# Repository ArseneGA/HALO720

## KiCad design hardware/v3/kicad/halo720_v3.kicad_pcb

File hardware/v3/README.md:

# HALO 720 v3 — cartes électroniques (rév. A)

- `kicad/` : carte principale CM4, 4 couches, 43 × 69,5 mm (KiCad 9). `kicad_flash/` : carte flash aluminium 24 × 14 mm.
- `fabrication/carte_CM4/` et `fabrication/flash/` : **fichiers à envoyer à l'usine** (Gerber zip, BOM, CPL, PDF, rendus 3D).
- `tools/` : tout est généré par script, du schéma aux fichiers d'usine.

Chaîne complète (KiCad 9 + Python 3, scipy, matplotlib) :

```bash
cd hardware/v3/tools
python3 gen_schematic.py ../kicad        # schémas des 2 cartes
python3 check_netlist.py; python3 check_netlist.py flash   # câblage = description
python3 gen_footprints.py                # empreintes DF40 (CM4), LED OSRAM
bash run_main.sh && python3 silk_main.py # placement + routage carte CM4 (≈ 10 min), DRC
python3 build_flash.py                   # carte flash, DRC
python3 make_fab.py                      # ERC + DRC + PDF schémas + Gerber/BOM/CPL/rendus (refuse si erreur)
```

Documentation : `docs/v3/SCHEMA_V3.md` (français), `docs/v3/FACTORY_ASSEMBLY_EN.md` (usine, anglais),
`docs/v3/IMAGE_EMMC.md`, `docs/v3/QUOTE_REQUEST_EN.md`. Logiciel : `camera/` et `camera/v3/`.
Brochage CM4 et empreintes DF40 repris de la carte officielle CM4IO (Raspberry Pi, CC BY 4.0).

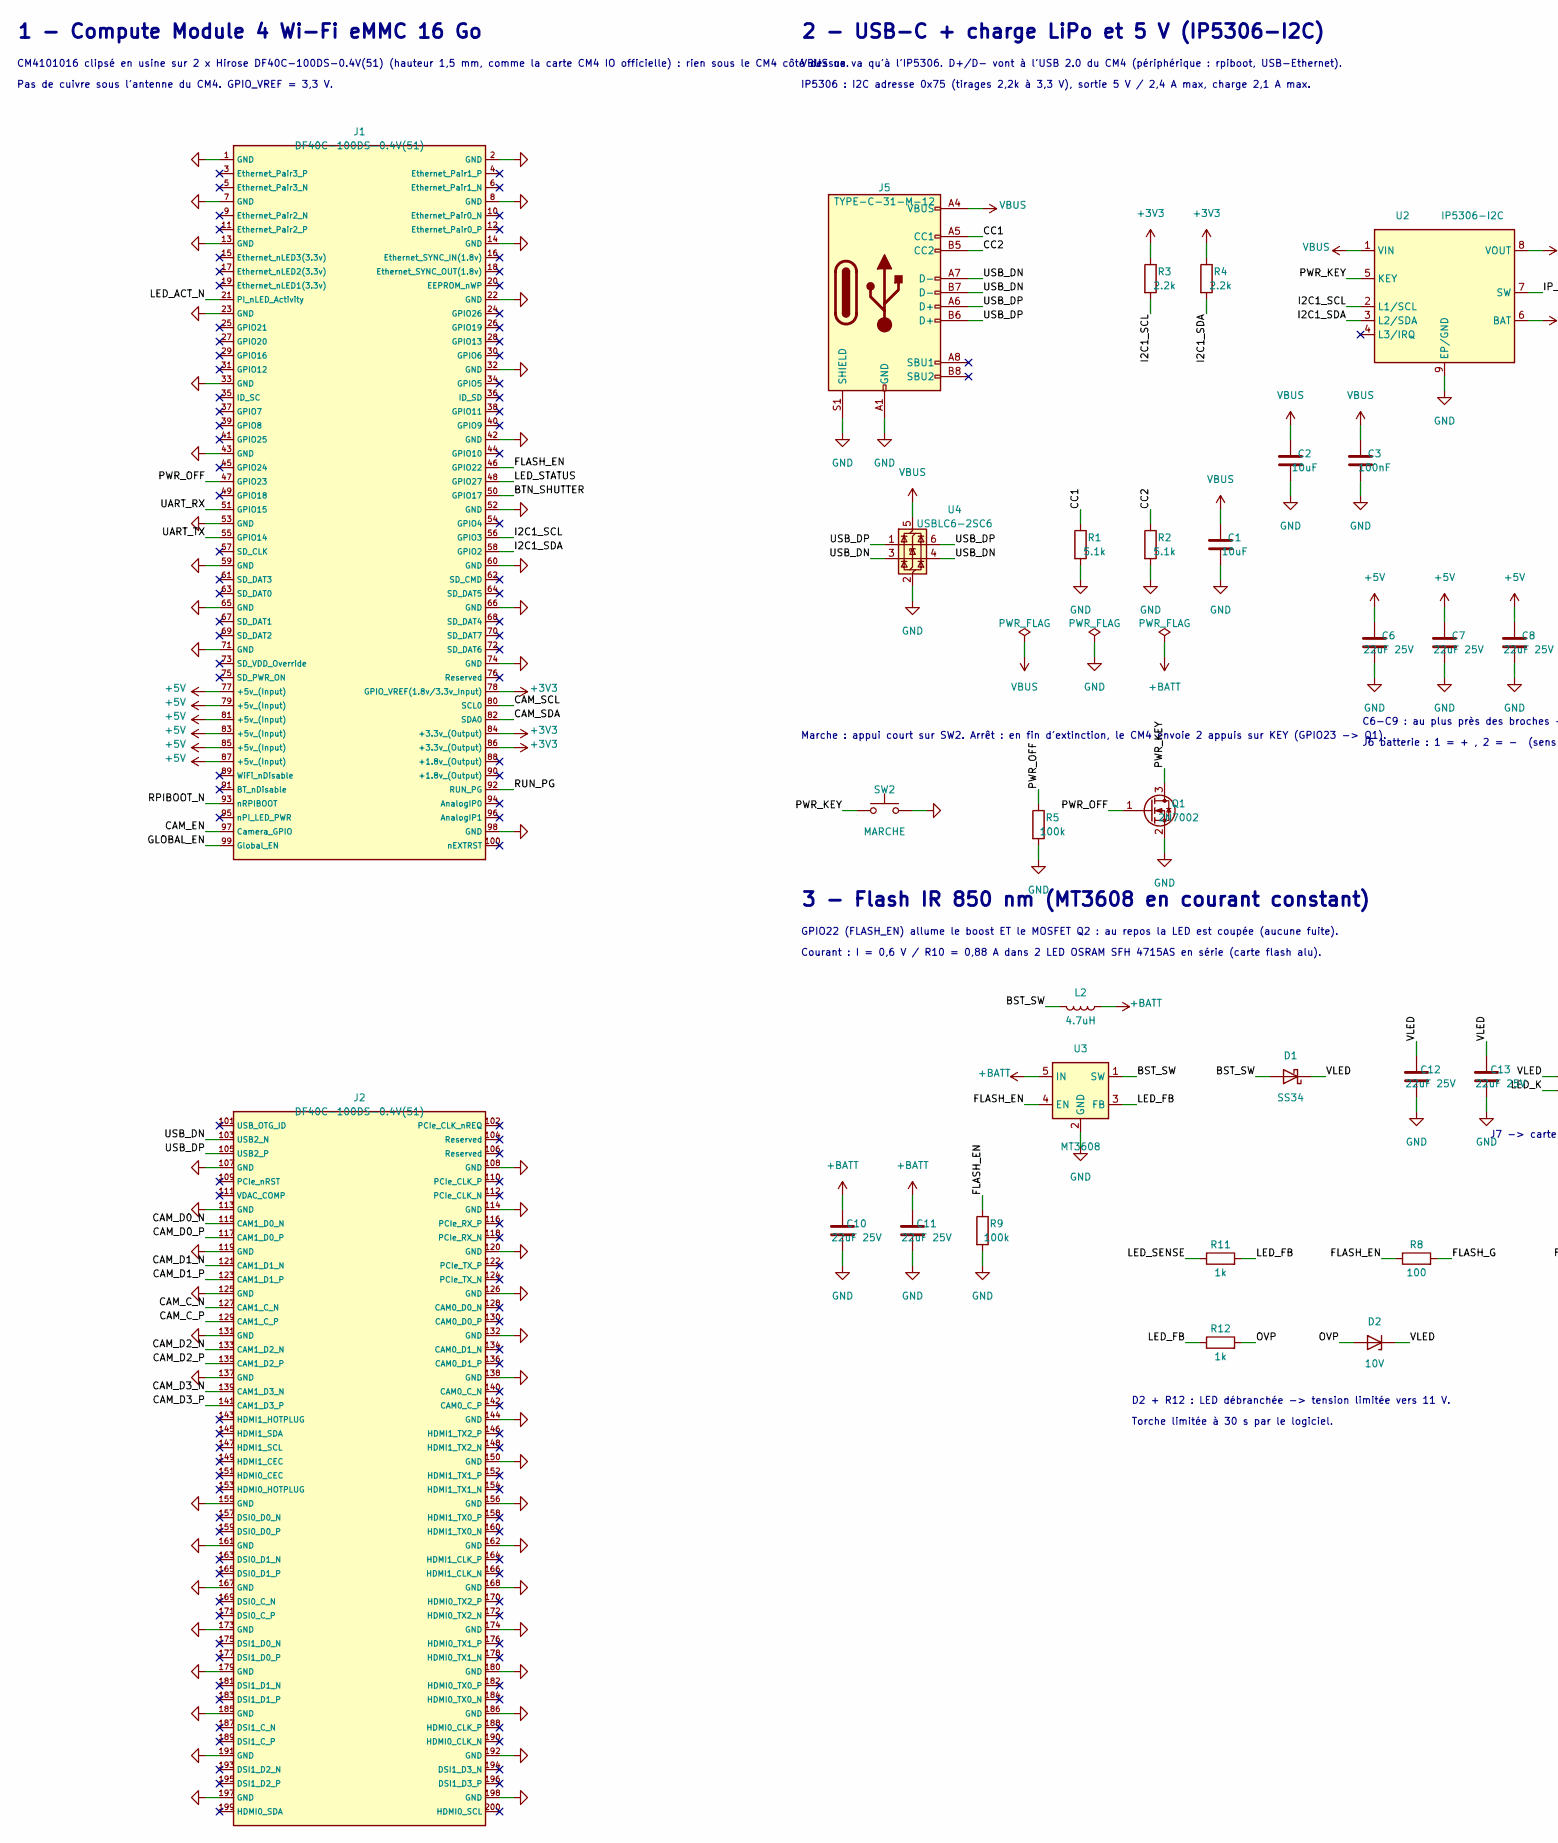
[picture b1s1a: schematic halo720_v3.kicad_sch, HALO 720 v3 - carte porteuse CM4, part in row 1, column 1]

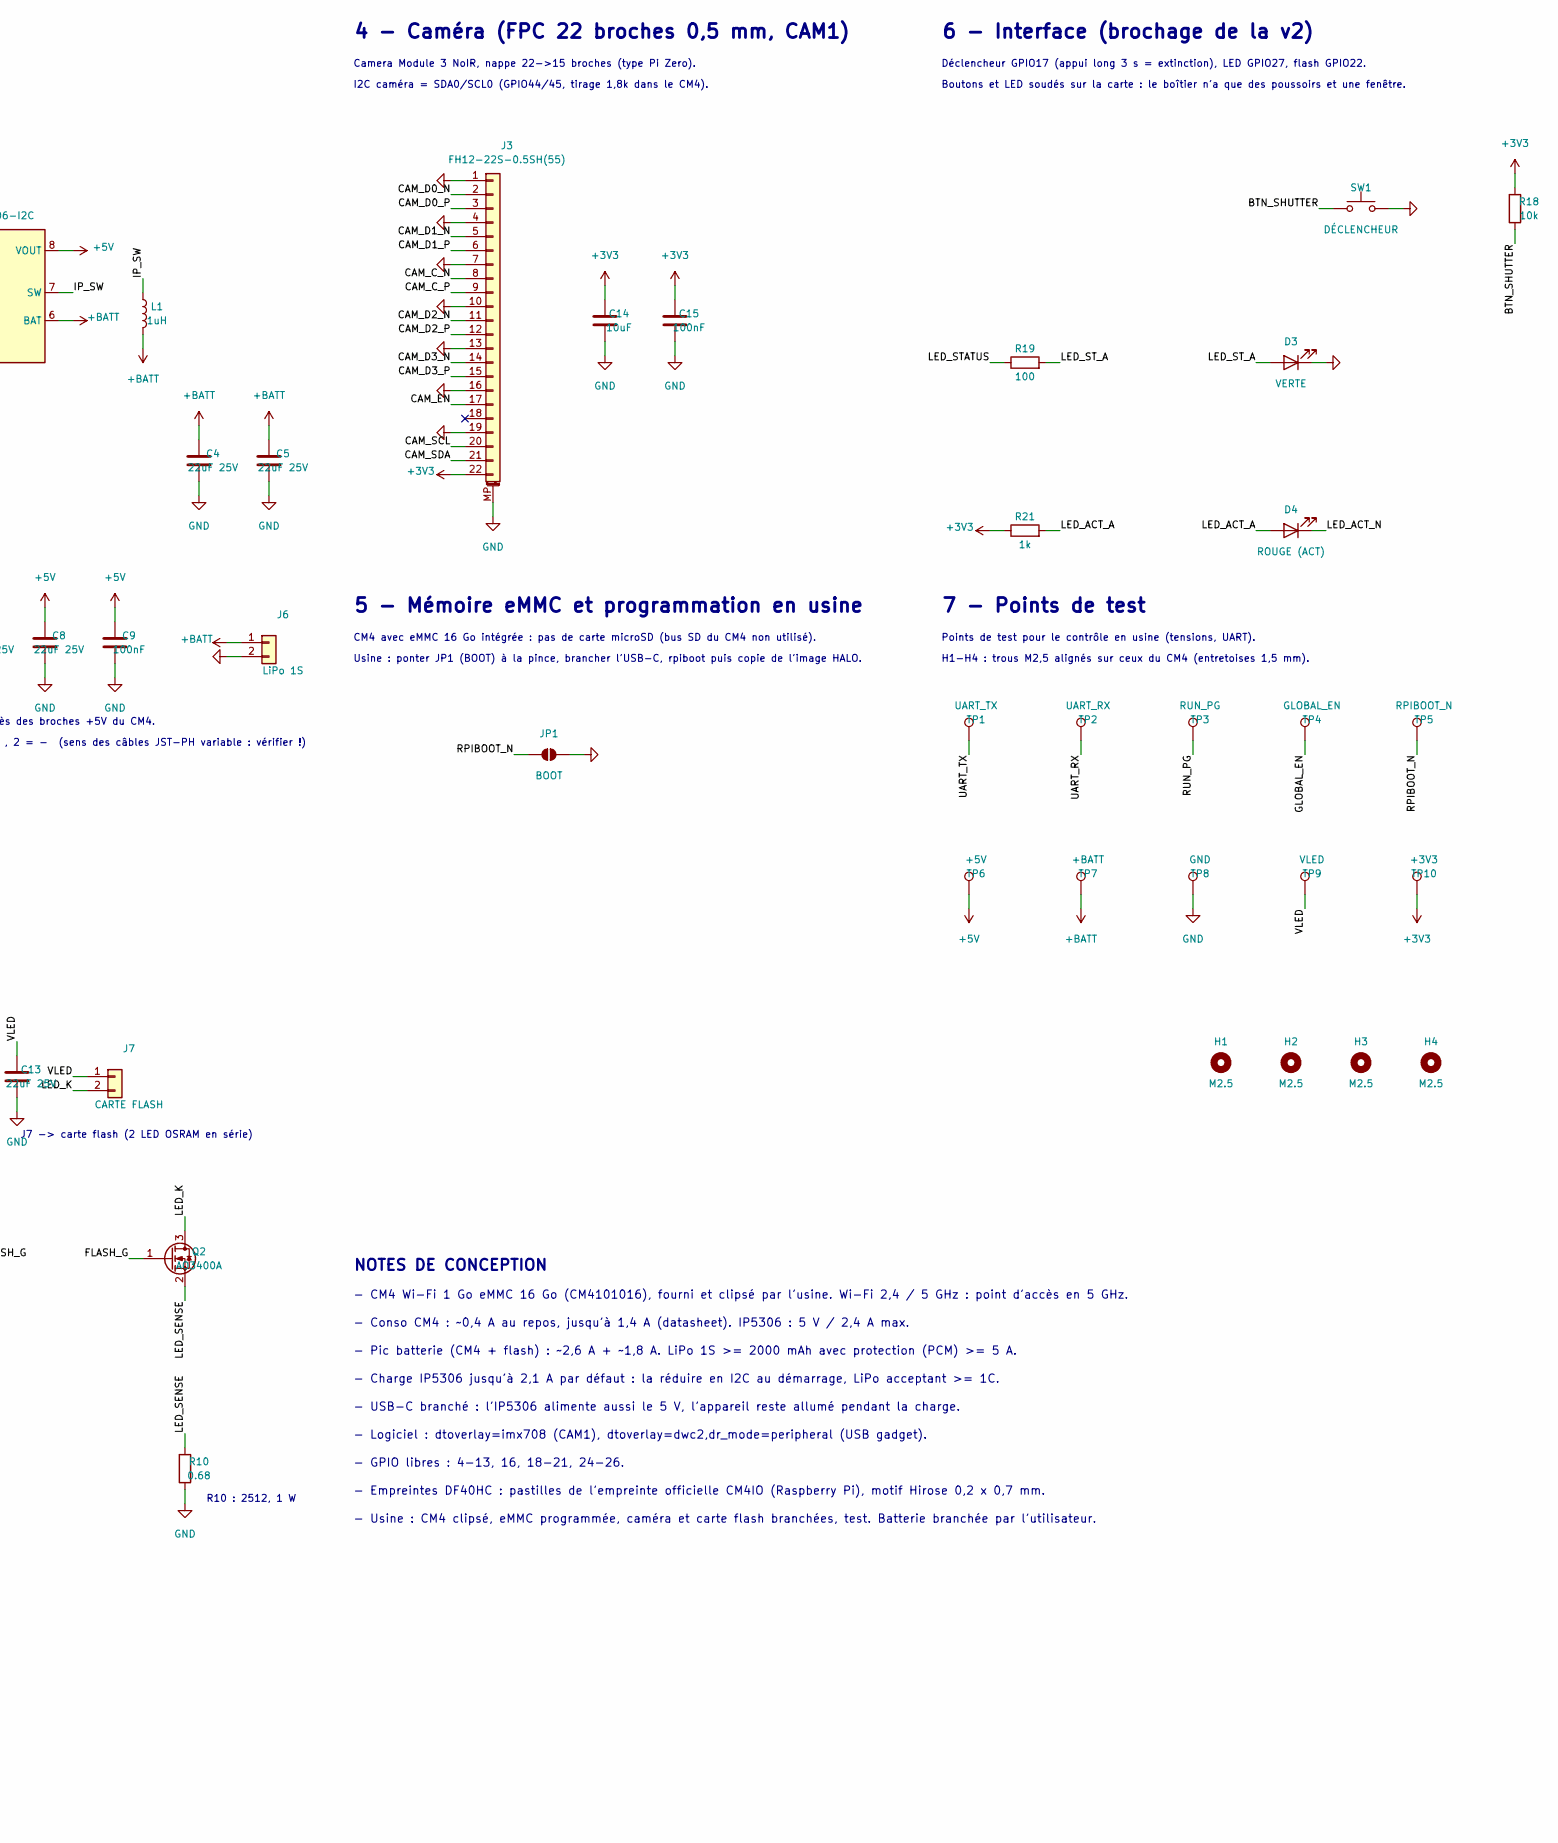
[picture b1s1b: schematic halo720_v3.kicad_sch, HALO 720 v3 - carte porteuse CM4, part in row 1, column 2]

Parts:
C1, C2, C14: 10uF; C_0603_1608Metric; LCSC C19702
C3, C9, C15: 100nF; C_0402_1005Metric; LCSC C1525
C4, C5, C6, C7, C8, C10, C11, C12, C13: 22uF 25V; C_0805_2012Metric; LCSC C45783
D1: SS34; D_SMA; MPN SS34; LCSC C8678
D2: 10V; D_SOD-123; MPN BZT52C10; LCSC C2103
D3: VERTE; LED_0603_1608Metric; MPN KT-0603G; LCSC C12624
D4: ROUGE (ACT); LED_0603_1608Metric; MPN KT-0603R; LCSC C2286
H1, H2, H3, H4: M2.5; MountingHole_2.7mm_M2.5
J1: DF40C-100DS-0.4V(51); Hirose_DF40HC3.0-100DS_CM4_J1; MPN DF40C-100DS-0.4V(51); LCSC C597931
J2: DF40C-100DS-0.4V(51); Hirose_DF40HC3.0-100DS_CM4_J2; MPN DF40C-100DS-0.4V(51); LCSC C597931
J3: FH12-22S-0.5SH(55); Hirose_FH12-22S-0.5SH_1x22-1MP_P0.50mm_Horizontal; MPN FH12-22S-0.5SH(55); LCSC C597981
J5: TYPE-C-31-M-12; USB_C_Receptacle_HRO_TYPE-C-31-M-12; MPN TYPE-C-31-M-12; LCSC C165948
J6: LiPo 1S; JST_PH_S2B-PH-SM4-TB_1x02-1MP_P2.00mm_Horizontal; MPN S2B-PH-SM4-TB(LF)(SN); LCSC C295747
J7: CARTE FLASH; JST_PH_S2B-PH-SM4-TB_1x02-1MP_P2.00mm_Horizontal; MPN S2B-PH-SM4-TB(LF)(SN); LCSC C295747
JP1: BOOT; SolderJumper-2_P1.3mm_Open_RoundedPad1.0x1.5mm
L1: 1uH; L_Changjiang_FNR6045S; MPN SMNR6045-1R0M; LCSC C135299
L2: 4.7uH; L_Sunlord_MWSA0518S; MPN SRP5030T-4R7M; LCSC C2045677
Q1: 2N7002; SOT-23; MPN 2N7002; LCSC C8545
Q2: AO3400A; SOT-23; MPN AO3400A; LCSC C20917
R1, R2: 5.1k; R_0402_1005Metric; LCSC C25905
R3, R4: 2.2k; R_0402_1005Metric; LCSC C25879
R5, R9: 100k; R_0402_1005Metric; LCSC C25741
R8, R19: 100; R_0402_1005Metric; LCSC C25076
R10: 0.68; R_2512_6332Metric; MPN RL2512FK-070R68L; LCSC C705617
R11, R12, R21: 1k; R_0402_1005Metric; LCSC C11702
R18: 10k; R_0402_1005Metric; LCSC C25744
SW1: DÉCLENCHEUR; SW_Push_1P1T_XKB_TS-1187A; MPN TS-1187A-B-A-B; LCSC C318884
SW2: MARCHE; SW_Push_1P1T_XKB_TS-1187A; MPN TS-1187A-B-A-B; LCSC C318884
TP1: UART_TX; TestPoint_Pad_D1.0mm
TP2: UART_RX; TestPoint_Pad_D1.0mm
TP3: RUN_PG; TestPoint_Pad_D1.0mm
TP4: GLOBAL_EN; TestPoint_Pad_D1.0mm
TP5: RPIBOOT_N; TestPoint_Pad_D1.0mm
TP6: +5V; TestPoint_Pad_D1.0mm
TP7: +BATT; TestPoint_Pad_D1.0mm
TP8: GND; TestPoint_Pad_D1.0mm
TP9: VLED; TestPoint_Pad_D1.0mm
TP10: +3V3; TestPoint_Pad_D1.0mm
U2: IP5306-I2C; SOIC-8-1EP_3.9x4.9mm_P1.27mm_EP2.41x3.3mm_ThermalVias; MPN IP5306-I2C; LCSC C488349
U3: MT3608; SOT-23-6; MPN MT3608; LCSC C84817
U4: USBLC6-2SC6; SOT-23-6; MPN USBLC6-2SC6; LCSC C7519

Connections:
+3V3: C14.1, C15.1, J1.78 (GPIO_VREF(1.8v/3.3v_Input)), J1.84 (+3.3v_(Output)), J1.86 (+3.3v_(Output)), J3.22, R3.1, R4.1, R18.1, R21.1, TP10.1
+5V: C6.1, C7.1, C8.1, C9.1, J1.77 (+5v_(Input)), J1.79 (+5v_(Input)), J1.81 (+5v_(Input)), J1.83 (+5v_(Input)), J1.85 (+5v_(Input)), J1.87 (+5v_(Input)), TP6.1, U2.8 (VOUT)
+BATT: C4.1, C5.1, C10.1, C11.1, J6.1, L1.2, L2.1, TP7.1, U2.6 (BAT), U3.5 (IN)
/BST_SW: D1.2 (A), L2.2, U3.1 (SW)
/BTN_SHUTTER: J1.50 (GPIO17), R18.2, SW1.1
/CAM_C_N: J2.127 (CAM1_C_N), J3.8
/CAM_C_P: J2.129 (CAM1_C_P), J3.9
/CAM_D0_N: J2.115 (CAM1_D0_N), J3.2
/CAM_D0_P: J2.117 (CAM1_D0_P), J3.3
/CAM_D1_N: J2.121 (CAM1_D1_N), J3.5
/CAM_D1_P: J2.123 (CAM1_D1_P), J3.6
/CAM_D2_N: J2.133 (CAM1_D2_N), J3.11
/CAM_D2_P: J2.135 (CAM1_D2_P), J3.12
/CAM_D3_N: J2.139 (CAM1_D3_N), J3.14
/CAM_D3_P: J2.141 (CAM1_D3_P), J3.15
/CAM_EN: J1.97 (Camera_GPIO), J3.17
/CAM_SCL: J1.80 (SCL0), J3.20
/CAM_SDA: J1.82 (SDA0), J3.21
/CC1: J5.A5 (CC1), R1.1
/CC2: J5.B5 (CC2), R2.1
/FLASH_EN: J1.46 (GPIO22), R8.1, R9.1, U3.4 (EN)
/FLASH_G: Q2.1 (G), R8.2
/GLOBAL_EN: J1.99 (Global_EN), TP4.1
/I2C1_SCL: J1.56 (GPIO3), R3.2, U2.2 (L1/SCL)
/I2C1_SDA: J1.58 (GPIO2), R4.2, U2.3 (L2/SDA)
/IP_SW: L1.1, U2.7 (SW)
/LED_ACT_A: D4.2 (A), R21.2
/LED_ACT_N: D4.1 (K), J1.21 (PI_nLED_Activity)
/LED_FB: R11.2, R12.1, U3.3 (FB)
/LED_K: J7.2, Q2.3 (D)
/LED_SENSE: Q2.2 (S), R10.1, R11.1
/LED_STATUS: J1.48 (GPIO27), R19.1
/LED_ST_A: D3.2 (A), R19.2
/OVP: D2.2 (A), R12.2
/PWR_KEY: Q1.3 (D), SW2.1, U2.5 (KEY)
/PWR_OFF: J1.47 (GPIO23), Q1.1 (G), R5.1
/RPIBOOT_N: J1.93 (nRPIBOOT), JP1.1 (A), TP5.1
/RUN_PG: J1.92 (RUN_PG), TP3.1
/UART_RX: J1.51 (GPIO15), TP2.1
/UART_TX: J1.55 (GPIO14), TP1.1
/USB_DN: J2.103 (USB2_N), J5.A7 (D-), J5.B7 (D-), U4.3 (I/O2), U4.4 (I/O2)
/USB_DP: J2.105 (USB2_P), J5.A6 (D+), J5.B6 (D+), U4.1 (I/O1), U4.6 (I/O1)
/VLED: C12.1, C13.1, D1.1 (K), D2.1 (K), J7.1, TP9.1
GND: C1.2, C2.2, C3.2, C4.2, C5.2, C6.2, C7.2, C8.2, C9.2, C10.2, C11.2, C12.2, C13.2, C14.2, C15.2, D3.1 (K), J1.1 (GND), J1.2 (GND), J1.7 (GND), J1.8 (GND), J1.13 (GND), J1.14 (GND), J1.22 (GND), J1.23 (GND), J1.32 (GND), J1.33 (GND), J1.42 (GND), J1.43 (GND), J1.52 (GND), J1.53 (GND), J1.59 (GND), J1.60 (GND), J1.65 (GND), J1.66 (GND), J1.71 (GND), J1.74 (GND), J1.98 (GND), J2.107 (GND), J2.108 (GND), J2.113 (GND), J2.114 (GND), J2.119 (GND), J2.120 (GND), J2.125 (GND), J2.126 (GND), J2.131 (GND), J2.132 (GND), J2.137 (GND), J2.138 (GND), J2.144 (GND), J2.150 (GND), J2.155 (GND), J2.156 (GND), J2.161 (GND), J2.162 (GND), J2.167 (GND), J2.168 (GND), J2.173 (GND), J2.174 (GND), J2.179 (GND), J2.180 (GND), J2.185 (GND), J2.186 (GND), J2.191 (GND), J2.192 (GND), J2.197 (GND), J2.198 (GND), J3.1, J3.4, J3.7, J3.10, J3.13, J3.16, J3.19, J3.MP (MountPin), J5.A1 (GND), J5.A12 (GND), J5.B1 (GND), J5.B12 (GND), J5.S1 (SHIELD), J6.2, JP1.2 (B), Q1.2 (S), R1.2, R2.2, R5.2, R9.2, R10.2, SW1.2, SW2.2, TP8.1, U2.9 (EP/GND), U3.2 (GND), U4.2 (GND)
VBUS: C1.1, C2.1, C3.1, J5.A4 (VBUS), J5.A9 (VBUS), J5.B4 (VBUS), J5.B9 (VBUS), U2.1 (VIN), U4.5 (VBUS)

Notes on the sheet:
1 - Compute Module 4 Wi-Fi eMMC 16 Go
CM4101016 clipsé en usine sur 2 x Hirose DF40C-100DS-0.4V(51) (hauteur 1,5 mm, comme la carte CM4 IO officielle) : rien sous le CM4 côté dessus.
Pas de cuivre sous l'antenne du CM4. GPIO_VREF = 3,3 V.
2 - USB-C + charge LiPo et 5 V (IP5306-I2C)
VBUS ne va qu'à l'IP5306. D+/D- vont à l'USB 2.0 du CM4 (périphérique : rpiboot, USB-Ethernet).
IP5306 : I2C adresse 0x75 (tirages 2,2k à 3,3 V), sortie 5 V / 2,4 A max, charge 2,1 A max.
C6-C9 : au plus près des broches +5V du CM4.
J6 batterie : 1 = + , 2 = - (sens des câbles JST-PH variable : vérifier !)
Marche : appui court sur SW2. Arrêt : en fin d'extinction, le CM4 envoie 2 appuis sur KEY (GPIO23 -> Q1).
3 - Flash IR 850 nm (MT3608 en courant constant)
GPIO22 (FLASH_EN) allume le boost ET le MOSFET Q2 : au repos la LED est coupée (aucune fuite).
Courant : I = 0,6 V / R10 = 0,88 A dans 2 LED OSRAM SFH 4715AS en série (carte flash alu).
J7 -> carte flash (2 LED OSRAM en série)
R10 : 2512, 1 W
D2 + R12 : LED débranchée -> tension limitée vers 11 V.
Torche limitée à 30 s par le logiciel.
4 - Caméra (FPC 22 broches 0,5 mm, CAM1)
Camera Module 3 NoIR, nappe 22->15 broches (type Pi Zero).
I2C caméra = SDA0/SCL0 (GPIO44/45, tirage 1,8k dans le CM4).
5 - Mémoire eMMC et programmation en usine
CM4 avec eMMC 16 Go intégrée : pas de carte microSD (bus SD du CM4 non utilisé).
Usine : ponter JP1 (BOOT) à la pince, brancher l'USB-C, rpiboot puis copie de l'image HALO.
6 - Interface (brochage de la v2)
Déclencheur GPIO17 (appui long 3 s = extinction), LED GPIO27, flash GPIO22.
Boutons et LED soudés sur la carte : le boîtier n'a que des poussoirs et une fenêtre.
7 - Points de test
Points de test pour le contrôle en usine (tensions, UART).
H1-H4 : trous M2,5 alignés sur ceux du CM4 (entretoises 1,5 mm).
NOTES DE CONCEPTION
- CM4 Wi-Fi 1 Go eMMC 16 Go (CM4101016), fourni et clipsé par l'usine. Wi-Fi 2,4 / 5 GHz : point d'accès en 5 GHz.
- Conso CM4 : ~0,4 A au repos, jusqu'à 1,4 A (datasheet). IP5306 : 5 V / 2,4 A max.
- Pic batterie (CM4 + flash) : ~2,6 A + ~1,8 A. LiPo 1S >= 2000 mAh avec protection (PCM) >= 5 A.
- Charge IP5306 jusqu'à 2,1 A par défaut : la réduire en I2C au démarrage, LiPo acceptant >= 1C.
- USB-C branché : l'IP5306 alimente aussi le 5 V, l'appareil reste allumé pendant la charge.
- Logiciel : dtoverlay=imx708 (CAM1), dtoverlay=dwc2,dr_mode=peripheral (USB gadget).
- GPIO libres : 4-13, 16, 18-21, 24-26.
- Empreintes DF40HC : pastilles de l'empreinte officielle CM4IO (Raspberry Pi), motif Hirose 0,2 x 0,7 mm.
- Usine : CM4 clipsé, eMMC programmée, caméra et carte flash branchées, test. Batterie branchée par l'utilisateur.

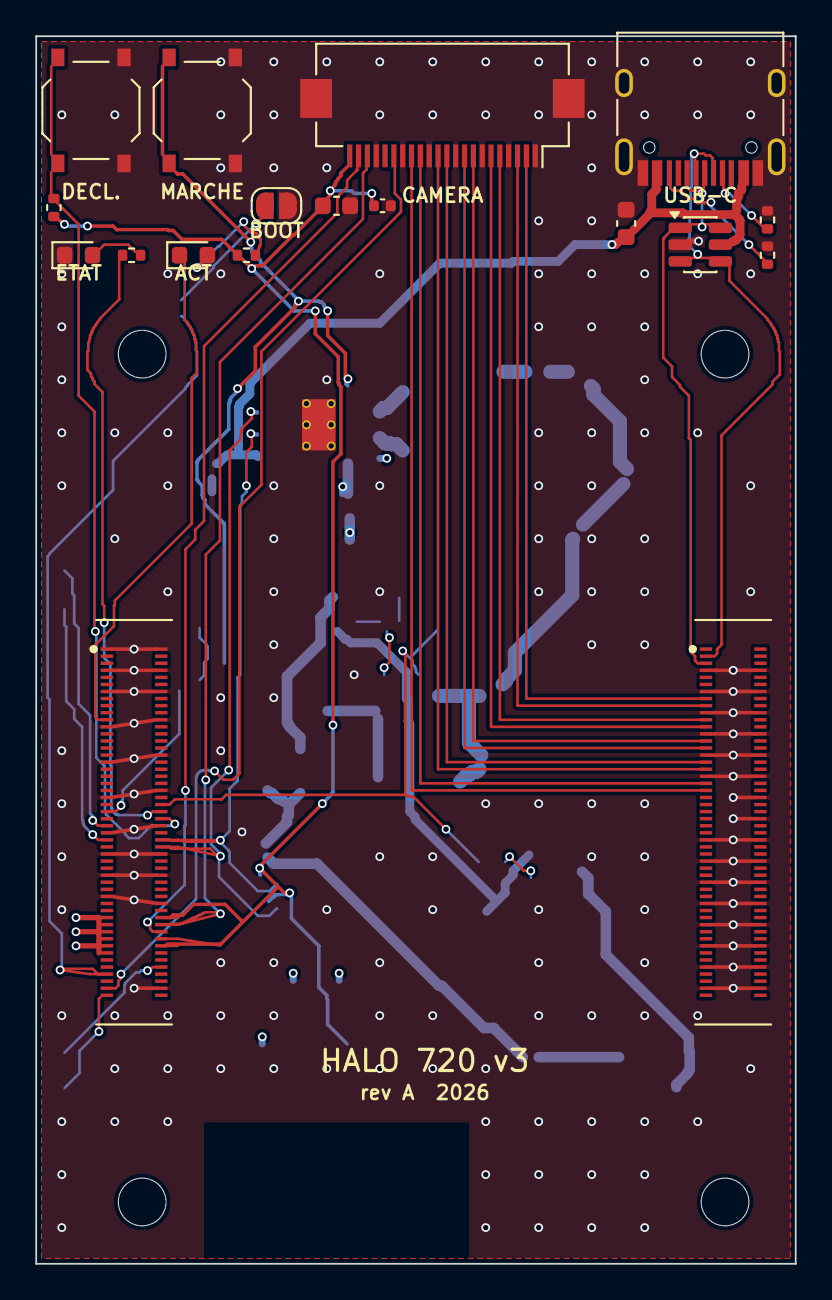
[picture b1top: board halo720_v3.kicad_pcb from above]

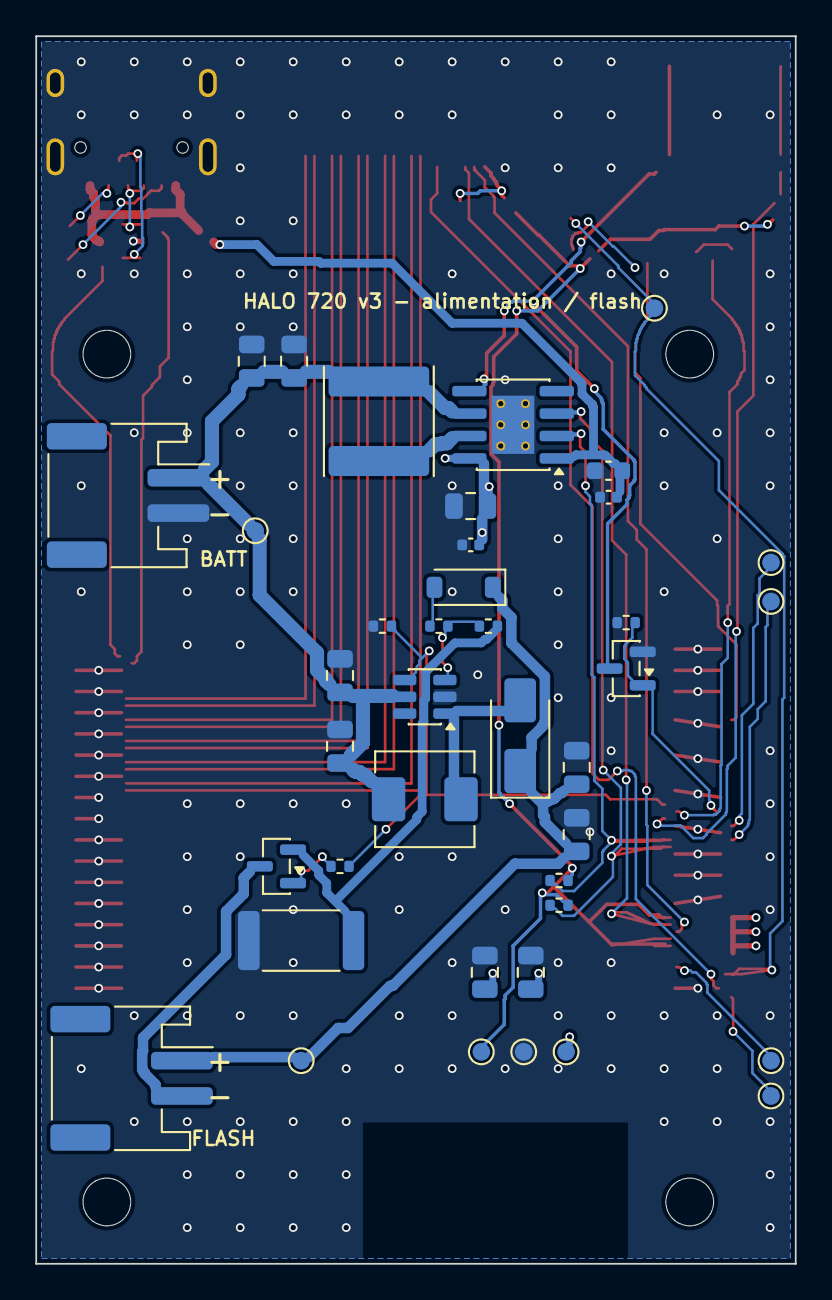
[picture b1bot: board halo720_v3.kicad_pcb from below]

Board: 4 copper layers, 43.0 x 69.5 mm, 62 parts (40 on the bottom side), 45 nets.

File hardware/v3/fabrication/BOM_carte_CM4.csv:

Comment,Designator,Footprint,LCSC Part #
10uF,"C1,C2,C14",C_0603_1608Metric,C19702
100nF,"C3,C9,C15",C_0402_1005Metric,C1525
22uF 25V,"C4,C5,C6,C7,C8,C10,C11,C12,C13",C_0805_2012Metric,C45783
SS34,D1,D_SMA,C8678
BZT52C10,D2,D_SOD-123,C2103
KT-0603G,D3,LED_0603_1608Metric,C72043
KT-0603R,D4,LED_0603_1608Metric,C2286
DF40HC(3.0)-100DS-0.4V(51),"J1,J2",Hirose_DF40HC3.0-100DS-0.4V,C424649
FH12-22S-0.5SH(55),J3,Hirose_FH12-22S-0.5SH_1x22-1MP_P0.50mm_Horizontal,C597981
TYPE-C-31-M-12,J5,USB_C_Receptacle_HRO_TYPE-C-31-M-12,C165948
S2B-PH-SM4-TB(LF)(SN),"J6,J7",JST_PH_S2B-PH-SM4-TB_1x02-1MP_P2.00mm_Horizontal,C295747
SMNR6045-1R0M,L1,L_Changjiang_FNR6045S,C135299
MWSA0518S-4R7MT,L2,L_Sunlord_MWSA0518S,C408347
2N7002,Q1,SOT-23,C8545
AO3400A,Q2,SOT-23,C20917
5.1k,"R1,R2",R_0402_1005Metric,C25905
2.2k,"R3,R4",R_0402_1005Metric,C25879
100k,"R5,R9",R_0402_1005Metric,C25741
100,R8,R_0402_1005Metric,C25076
RL2512FK-070R68L,R10,R_2512_6332Metric,C705617
1k,"R11,R12,R19,R21",R_0402_1005Metric,C11702
10k,R18,R_0402_1005Metric,C25744
TS-1187A-B-A-B,"SW1,SW2,SW3",SW_Push_1P1T_XKB_TS-1187A,C318884
IP5306-I2C,U2,SOIC-8-1EP_3.9x4.9mm_P1.27mm_EP2.41x3.3mm_ThermalVias,C488349
MT3608,U3,SOT-23-6,C84817
USBLC6-2SC6,U4,SOT-23-6,C7519

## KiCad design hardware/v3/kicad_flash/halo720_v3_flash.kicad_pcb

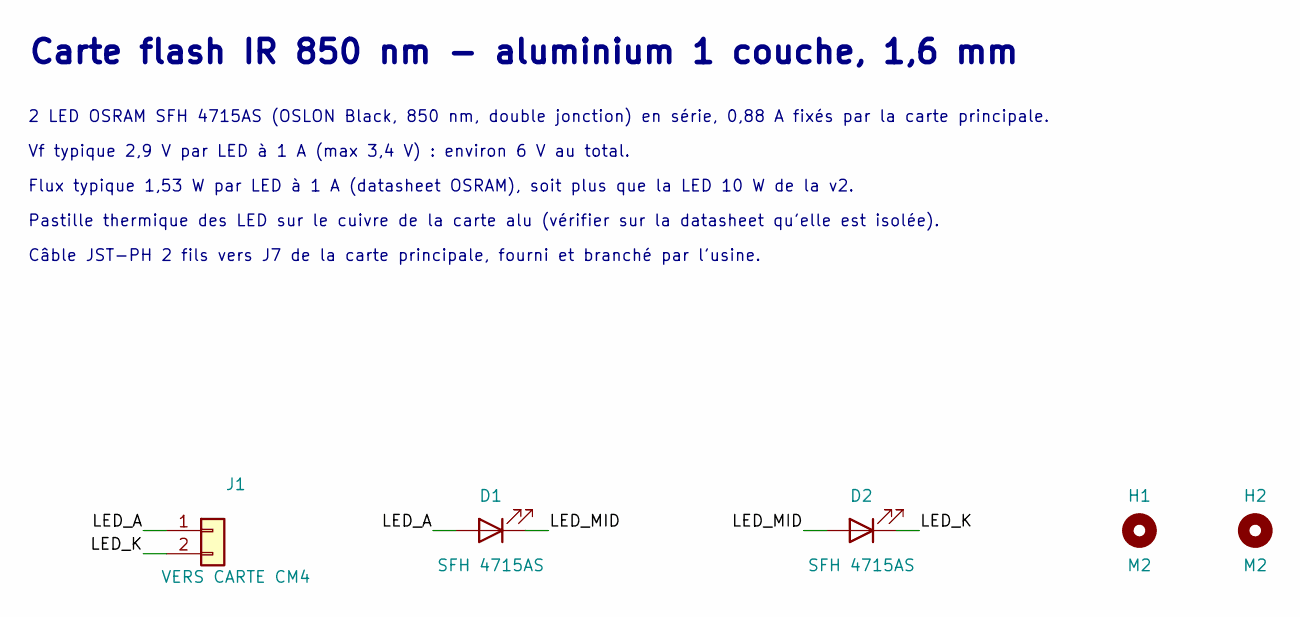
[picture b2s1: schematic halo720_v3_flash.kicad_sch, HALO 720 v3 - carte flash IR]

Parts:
D1, D2: SFH 4715AS; OSRAM_OSLON_Black_SFH4715AS; MPN SFH 4715AS; LCSC C2880156
H1, H2: M2; MountingHole_2.2mm_M2
J1: VERS CARTE CM4; JST_PH_S2B-PH-SM4-TB_1x02-1MP_P2.00mm_Horizontal; MPN S2B-PH-SM4-TB(LF)(SN); LCSC C295747

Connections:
/LED_A: D1.2 (A), J1.1
/LED_K: D2.1 (K), J1.2
/LED_MID: D1.1 (K), D2.2 (A)

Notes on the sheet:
Carte flash IR 850 nm - aluminium 1 couche, 1,6 mm
2 LED OSRAM SFH 4715AS (OSLON Black, 850 nm, double jonction) en série, 0,88 A fixés par la carte principale.
Vf typique 2,9 V par LED à 1 A (max 3,4 V) : environ 6 V au total.
Flux typique 1,53 W par LED à 1 A (datasheet OSRAM), soit plus que la LED 10 W de la v2.
Pastille thermique des LED sur le cuivre de la carte alu (vérifier sur la datasheet qu'elle est isolée).
Câble JST-PH 2 fils vers J7 de la carte principale, fourni et branché par l'usine.

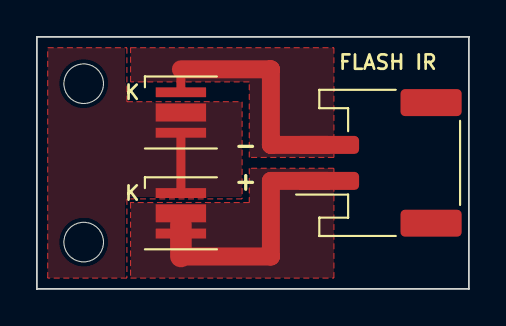
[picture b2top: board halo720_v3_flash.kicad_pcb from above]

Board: 2 copper layers, 24.0 x 14.0 mm, 5 parts (0 on the bottom side), 3 nets.

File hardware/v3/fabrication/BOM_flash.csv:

Comment,Designator,Footprint,LCSC Part #
SFH 4715AS,"D1,D2",OSRAM_OSLON_Black_SFH4715AS,C2880156
S2B-PH-SM4-TB(LF)(SN),J1,JST_PH_S2B-PH-SM4-TB_1x02-1MP_P2.00mm_Horizontal,C295747

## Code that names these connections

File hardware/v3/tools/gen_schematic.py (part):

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        "77": "+5V", "79": "+5V", "81": "+5V", "83": "+5V", "85": "+5V", "87": "+5V",
        "84": "+3V3", "86": "+3V3", "78": "+3V3",
        "21": "LED_ACT_N",
        "46": "FLASH_EN",       # GPIO22 (comme la v2)
        "47": "PWR_OFF",        # GPIO23 -> appui KEY de l'IP5306 (extinction)
        "48": "LED_STATUS",     # GPIO27 (comme la v2)
        "50": "BTN_SHUTTER",    # GPIO17 (comme la v2)
        "56": "I2C1_SCL",       # GPIO3
        "58": "I2C1_SDA",       # GPIO2
        "55": "UART_TX",        # GPIO14
        "51": "UART_RX",        # GPIO15
        "80": "CAM_SCL", "82": "CAM_SDA", "97": "CAM_EN",
        "92": "RUN_PG", "93": "RPIBOOT_N", "99": "GLOBAL_EN",
    })
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
    # bouton marche + extinction logicielle
    kx, ky = ox, oy + 134.62
    s.text("Marche : appui court sur SW2. Arrêt : en fin d'extinction, le CM4 envoie 2 appuis sur KEY (GPIO23 -> Q1).", kx, ky - 7.62)
    s.part("SW2", "Switch:SW_Push", "MARCHE", kx + 15.24, ky + 5.08, {"1": "PWR_KEY", "2": "GND"},
           fp="Button_Switch_SMD:SW_Push_1P1T_XKB_TS-1187A", lcsc="C318884", mpn="TS-1187A-B-A-B",
           ref_at=(kx + 15.24, ky + 1.27), val_at=(kx + 15.24, ky + 8.89))
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    # ================= Bloc 3 : flash IR =================
    fx, fy = 160.02, 182.88
    title(3, "Flash IR 850 nm (MT3608 en courant constant)", fx, fy,
          ["GPIO22 (FLASH_EN) allume le boost ET le MOSFET Q2 : au repos la LED est coupée (aucune fuite).",
           "Courant : I = 0,6 V / R10 = 0,88 A dans 2 LED OSRAM SFH 4715AS en série (carte flash alu)."])
    s.part("U3", "Regulator_Switching:MT3608", "MT3608", fx + 50.8, fy + 33.02,
           {"1": "BST_SW", "2": "GND", "3": "LED_FB", "4": "FLASH_EN", "5": "+BATT"},
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    # ================= Bloc 6 : interface =================
    ix, iy = 452.12, 25.4
    title(6, "Interface (brochage de la v2)", ix, iy,
          ["Déclencheur GPIO17 (appui long 3 s = extinction), LED GPIO27, flash GPIO22.",
           "Boutons et LED soudés sur la carte : le boîtier n'a que des poussoirs et une fenêtre."])
    s.part("SW1", "Switch:SW_Push", "DÉCLENCHEUR", ix + 76.2, iy + 30.48, {"1": "BTN_SHUTTER", "2": "GND"},
           fp="Button_Switch_SMD:SW_Push_1P1T_XKB_TS-1187A", lcsc="C318884", mpn="TS-1187A-B-A-B",
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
